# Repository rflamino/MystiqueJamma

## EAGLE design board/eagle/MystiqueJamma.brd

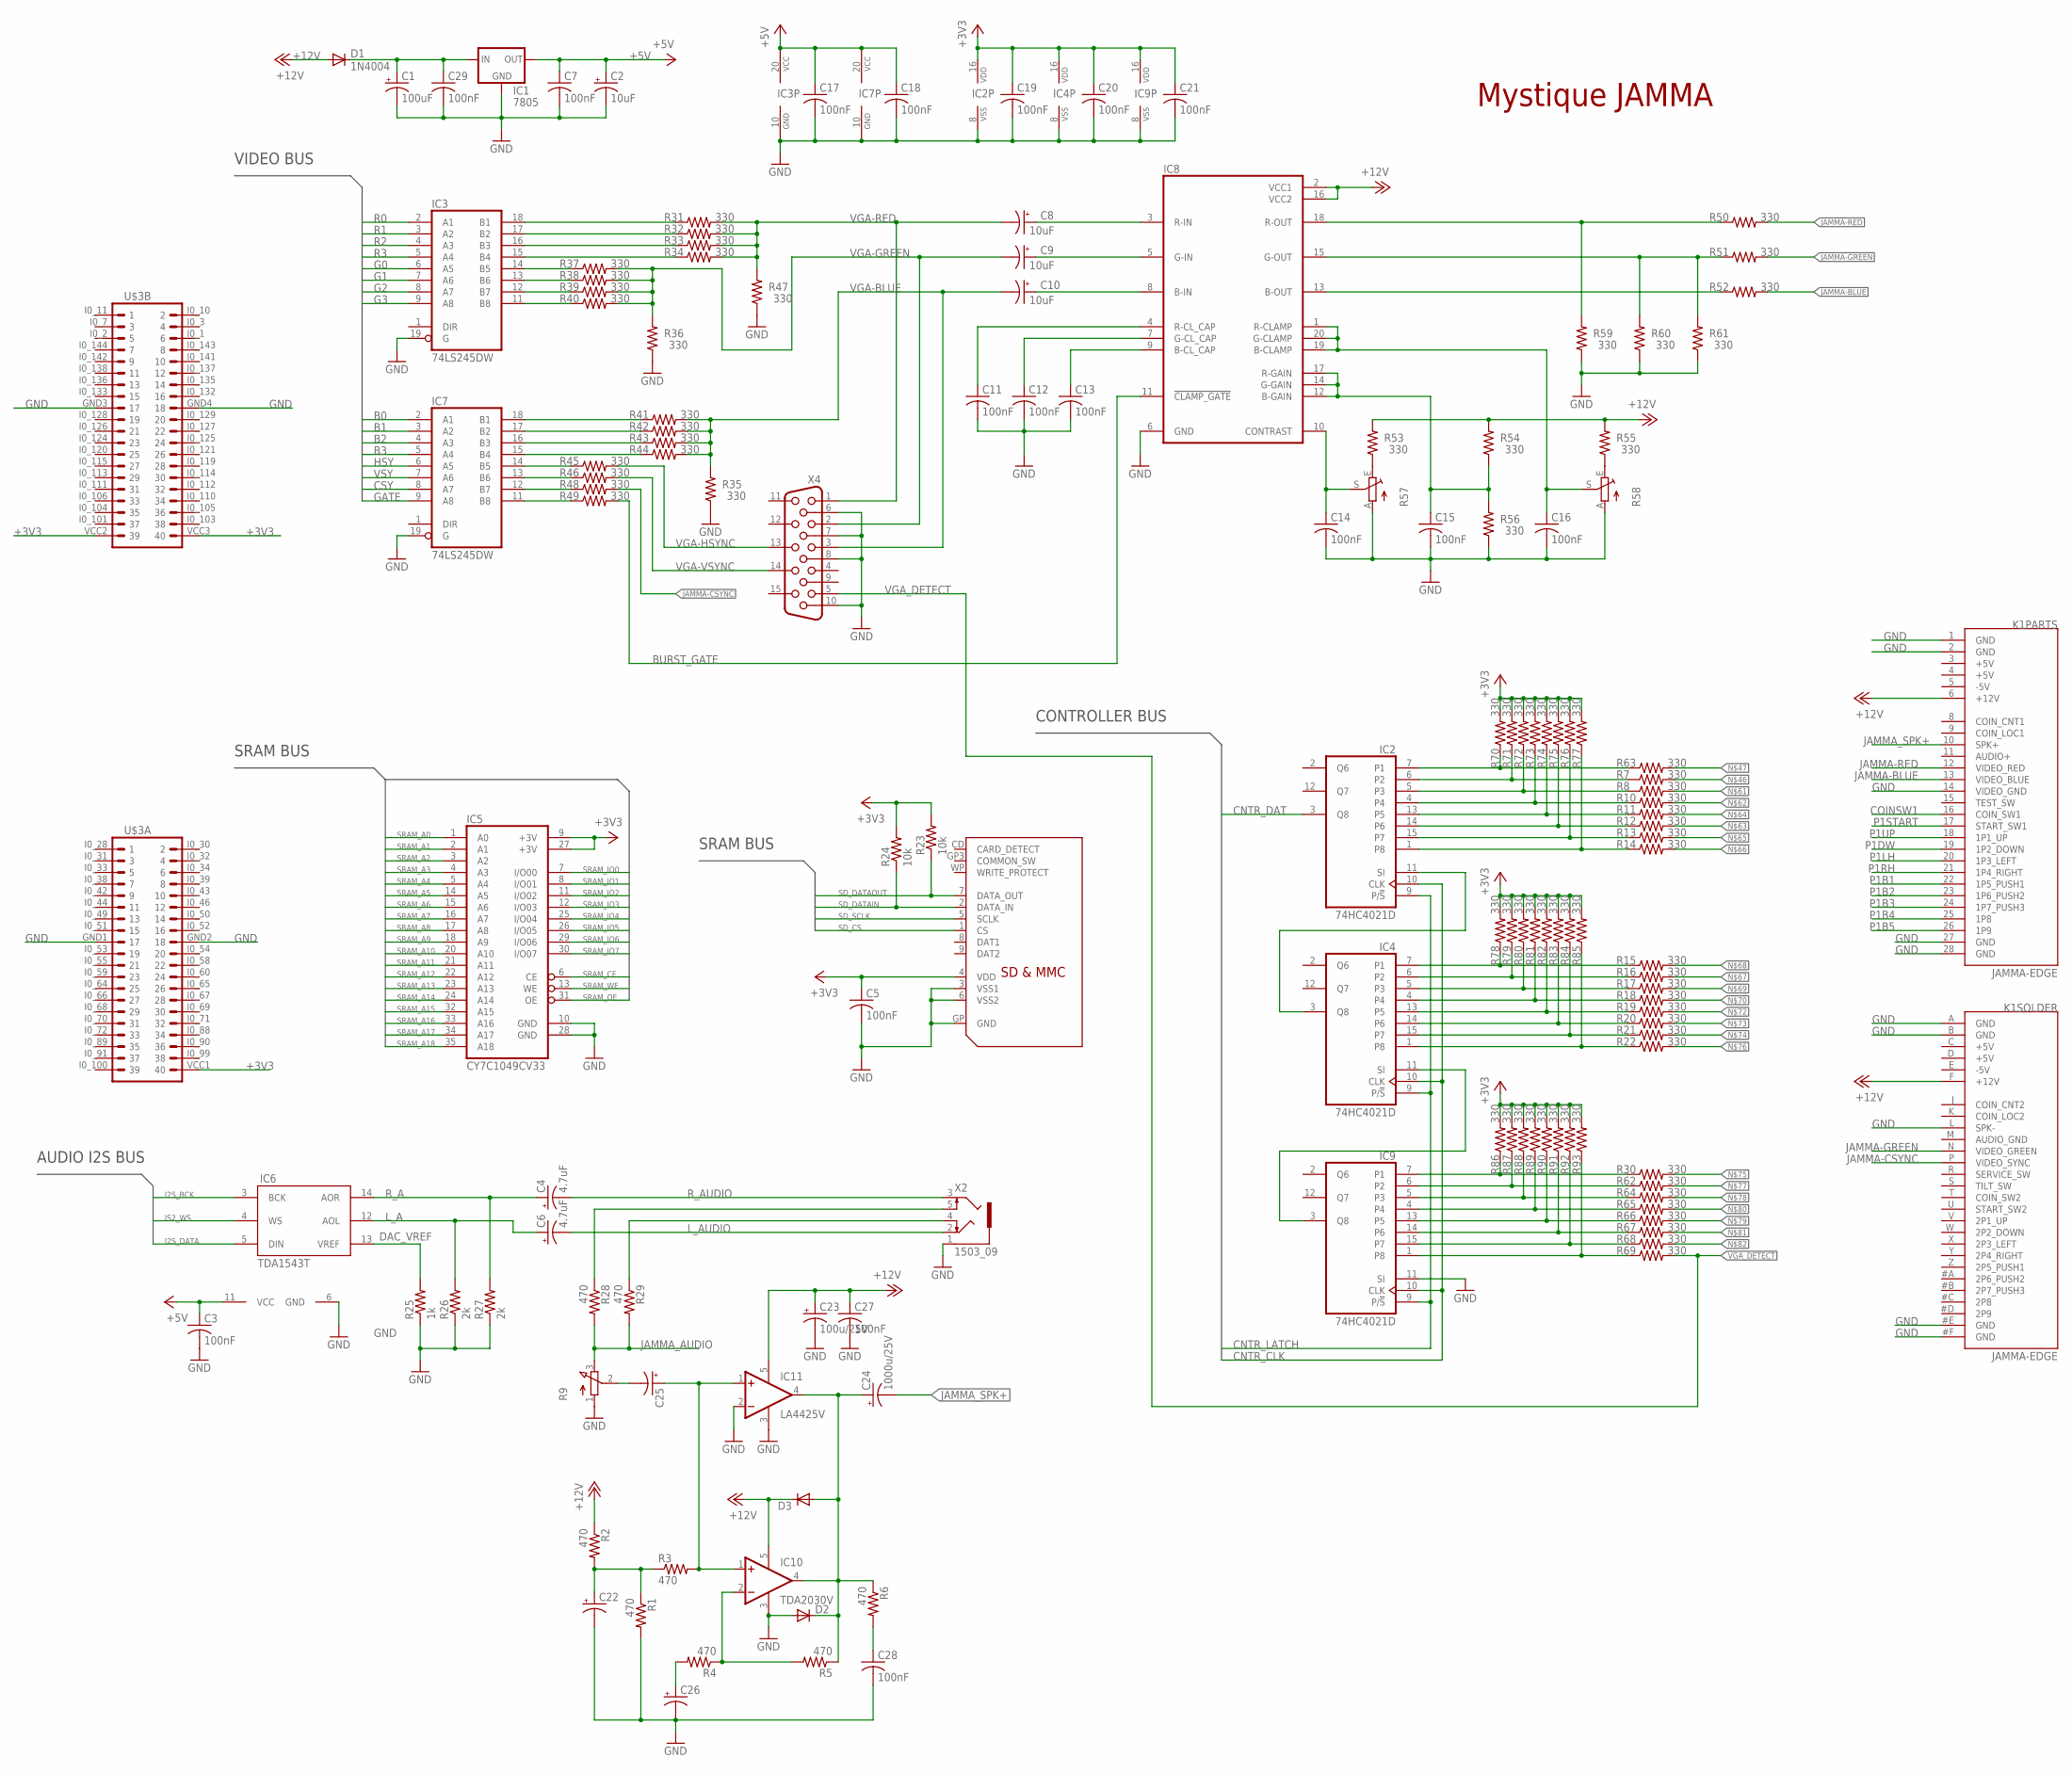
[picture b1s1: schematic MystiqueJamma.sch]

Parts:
C1: 100uF; E2,5-5
C2, C8, C9, C10: 10uF; E2,5-5
C3, C5, C7, C11, C12, C13, C14, C15, C16, C17, C18, C19, C20, C21, C27, C28, C29: 100nF; C1206
C4, C6: 4.7uF; E5-6
C22, C25, C26: CPOL-USE2-4; E2-4
C23: 100u/25V; E3,5-8
C24: 1000u/25V; E3,5-8
D1: 1N4004; DO41-10
D2, D3: DIODE-SOD80C; SOD80C
IC1: 7805; TO220-IGO
IC2, IC4, IC9: 74HC4021D; SO16
IC3, IC7: 74LS245DW; SO20W
IC5: CY7C1049CV33; SOJV36-400
IC6: TDA1543T; SOIC-16NW
IC8: TLS1233; DIL20
IC10: TDA2030V; CB360
IC11: LA4425V; LA4425
K1: JAMMA-EDGE
R1, R2, R3, R4, R5, R6, R28: 470; R1206
R7, R8, R10, R11, R12, R13, R14, R15, R16, R17, R18, R19, R20, R21, R22, R30, R31, R32, R33, R34, R35, R36, R37, R38, R39, R40, R41, R42, R43, R44, R45, R46, R47, R48, R49, R50, R51, R52, R53, R54, R55, R56, R59, R60, R61, R62, R63, R64, R65, R66, R67, R68, R69, R70, R71, R72, R73, R74, R75, R76, R77, R78, R79, R80, R81, R82, R83, R84, R85, R86, R87, R88, R89, R90, R91, R92, R93: 330; M1206
R9: 3RP/1610N
R23, R24: 10k; R1206
R25: 1k; R1206
R26, R27: 2k; R1206
R29: 470; M1206
R57, R58: TRIM_EU-B90P; SP19L
U$2: SDMMC06132; 06132
U$3: C4E6-K""; E6V33
X2: 1503_09
X4: HF15H; HDF15H

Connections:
+3V3: C5.1, C19.1, C20.1, C21.1, IC2.16 (VDD), IC4.16 (VDD), IC5.9 (+3V), IC5.27 (+3V), IC9.16 (VDD), R23.2, R24.2, R70.2, R71.2, R72.2, R73.2, R74.2, R75.2, R76.2, R77.2, R78.2, R79.2, R80.2, R81.2, R82.2, R83.2, R84.2, R85.2, R86.2, R87.2, R88.2, R89.2, R90.2, R91.2, R92.2, R93.2, U$2.4 (VDD), U$3.VCC1 (40), U$3.VCC2 (39), U$3.VCC3 (40)
+5V: C2.+, C3.1, C7.1, C17.1, C18.1, IC1.OUT, IC3.20 (VCC), IC6.11 (VCC), IC7.20 (VCC), K1.3 (+5V), K1.4 (+5V), K1.C (+5V), K1.D (+5V)
+12V: C23.+, C27.1, D1.A, D3.C, IC8.2 (VCC1), IC8.16 (VCC2), IC10.5 (V+), IC11.5 (V+), K1.6 (+12V), K1.F (+12V), R2.1, R53.2, R54.2, R55.2
-5V: K1.5 (-5V), K1.E (-5V)
B0: IC7.2 (A1)
B1: IC7.3 (A2)
B2: IC7.4 (A3)
B3: IC7.5 (A4)
BURST_GATE: IC8.11 (!CLAMP_GATE)
CNTR_CLK: IC2.10 (CLK), IC4.10 (CLK), IC9.10 (CLK)
CNTR_DAT: IC2.3 (Q8)
CNTR_LATCH: IC2.9 (P/!S), IC4.9 (P/!S), IC9.9 (P/!S)
COINSW1: K1.16 (COIN_SW1)
CSY: IC7.8 (A7)
DAC_VREF: IC6.13 (VREF), R25.2
G0: IC3.6 (A5)
G1: IC3.7 (A6)
G2: IC3.8 (A7)
G3: IC3.9 (A8)
GATE: IC7.9 (A8)
GND: C1.-, C2.-, C3.2, C5.2, C7.2, C11.2, C12.2, C13.2, C14.2, C15.2, C16.2, C17.2, C18.2, C19.2, C20.2, C21.2, C22.-, C23.-, C26.-, C27.2, C28.2, C29.2, D2.A, IC1.GND, IC2.8 (VSS), IC3.10 (GND), IC3.19 (G), IC4.8 (VSS), IC5.10 (GND), IC5.28 (GND), IC6.6 (GND), IC7.10 (GND), IC7.19 (G), IC8.6 (GND), IC9.8 (VSS), IC9.11 (SI), IC10.3 (GND), IC11.2 (-IN), IC11.3 (GND), K1.1 (GND), K1.2 (GND), K1.14 (VIDEO_GND), K1.27 (GND), K1.28 (GND), K1.#E (GND), K1.#F (GND), K1.A (GND), K1.B (GND), K1.L (SPK-), R1.2, R9.1 (A), R25.1, R26.1, R27.1, R35.1, R36.1, R47.1, R56.1, R57.A, R58.A, R59.1, R60.1, R61.1, U$2.3 (VSS1), U$2.6 (VSS2), U$2.GP (GND), U$3.GND1 (17), U$3.GND2 (18), U$3.GND3 (17), U$3.GND4 (18), X2.1, X4.6, X4.7, X4.8, X4.10
HSY: IC7.6 (A5)
I2S_BCK: IC6.3 (BCK)
I2S_DATA: IC6.5 (DIN)
IS2_WS: IC6.4 (WS)
JAMMA-BLUE: K1.13 (VIDEO_BLUE), R52.2
JAMMA-CSYNC: K1.P (VIDEO_SYNC)
JAMMA-GREEN: K1.N (VIDEO_GREEN), R51.2
JAMMA-RED: K1.12 (VIDEO_RED), R50.2
JAMMA_AUDIO: R9.3 (E), R28.2, R29.2
JAMMA_SPK+: C24.-, K1.10 (SPK+)
LAA: R29.1, X2.4
L_A: C6.+, IC6.12 (AOL), R26.2
L_AUDIO: C6.-, X2.2
unnamed: IC3.17 (B2), R32.1
unnamed: C1.+, C29.1, D1.C, IC1.IN
unnamed: IC3.18 (B1), R31.1
unnamed: C8.+, IC8.3 (R-IN)
unnamed: C9.+, IC8.5 (G-IN)
unnamed: C10.+, IC8.8 (B-IN)
unnamed: IC3.16 (B3), R33.1
unnamed: IC3.15 (B4), R34.1
unnamed: C16.1, IC8.1 (R-CLAMP), IC8.19 (B-CLAMP), IC8.20 (G-CLAMP), R58.S
unnamed: C11.1, IC8.4 (R-CL_CAP)
unnamed: C12.1, IC8.7 (G-CL_CAP)
unnamed: C13.1, IC8.9 (B-CL_CAP)
unnamed: IC8.18 (R-OUT), R50.1, R59.2
unnamed: IC8.15 (G-OUT), R51.1, R60.2, R61.2
unnamed: IC8.13 (B-OUT), R52.1
unnamed: C14.1, IC8.10 (CONTRAST), R57.S
unnamed: R53.1, R57.E
unnamed: IC2.7 (P1), R63.1
unnamed: R55.1, R58.E
unnamed: IC2.6 (P2), R7.1
unnamed: IC2.5 (P3), R8.1
unnamed: C15.1, IC8.12 (B-GAIN), IC8.14 (G-GAIN), IC8.17 (R-GAIN), R54.1, R56.2
unnamed: IC2.4, R10.1
unnamed: IC2.13 (P5), R11.1
unnamed: IC2.14 (P6), R12.1
unnamed: IC2.15 (P7), R13.1
unnamed: IC2.1 (P8), R14.1
unnamed: C22.+, R1.1, R2.2, R3.1
unnamed: C28.1, R6.2
unnamed: C26.+, R4.2
unnamed: IC10.2 (-IN), R4.1, R5.2
unnamed: IC2.11 (SI), IC4.3 (Q8)
unnamed: IC4.11 (SI), IC9.3 (Q8)
unnamed: C25.-, R9.2 (S)
unnamed: C25.+, IC10.1 (+IN), IC11.1 (+IN), R3.2
unnamed: C24.+, D2.C, D3.A, IC10.4 (OUT), IC11.4 (OUT), R5.1, R6.1
P1B1: K1.22 (1P5_PUSH1)
P1B2: K1.23 (1P6_PUSH2)
P1B3: K1.24 (1P7_PUSH3)
P1B4: K1.25 (1P8)
P1B5: K1.26 (1P9)
P1DW: K1.19 (1P2_DOWN)
P1LH: K1.20 (1P3_LEFT)
P1RH: K1.21 (1P4_RIGHT)
P1START: K1.17 (START_SW1)
P1UP: K1.18 (1P1_UP)
R0: IC3.2 (A1)
R1: IC3.3 (A2)
R2: IC3.4 (A3)
R3: IC3.5 (A4)
RAA: R28.1, X2.5
R_A: C4.+, IC6.14 (AOR), R27.2
R_AUDIO: C4.-, X2.3
SD_CS: U$2.1 (CS)
SD_DATAIN: R24.1, U$2.2 (DATA_IN)
SD_DATAOUT: R23.1, U$2.7 (DATA_OUT)
SD_SCLK: U$2.5 (SCLK)
SRAM_A0: IC5.1 (A0)
SRAM_A1: IC5.2 (A1)
SRAM_A2: IC5.3 (A2)
SRAM_A3: IC5.4 (A3)
SRAM_A4: IC5.5 (A4)
SRAM_A5: IC5.14 (A5)
SRAM_A6: IC5.15 (A6)
SRAM_A7: IC5.16 (A7)
SRAM_A8: IC5.17 (A8)
SRAM_A9: IC5.18 (A9)
SRAM_A10: IC5.20 (A10)
SRAM_A11: IC5.21 (A11)
SRAM_A12: IC5.22 (A12)
SRAM_A13: IC5.23 (A13)
SRAM_A14: IC5.24 (A14)
SRAM_A15: IC5.32 (A15)
SRAM_A16: IC5.33 (A16)
SRAM_A17: IC5.34 (A17)
SRAM_A18: IC5.35 (A18)
SRAM_CE: IC5.6 (CE)
SRAM_IO0: IC5.7 (I/O00)
SRAM_IO1: IC5.8 (I/O01)
SRAM_IO2: IC5.11 (I/O02)
SRAM_IO3: IC5.12 (I/O03)
SRAM_IO4: IC5.25 (I/O04)
SRAM_IO5: IC5.26 (I/O05)
SRAM_IO6: IC5.29 (I/O06)
SRAM_IO7: IC5.30 (I/O07)
SRAM_OE: IC5.31 (OE)
SRAM_WE: IC5.13 (WE)
VGA-BLUE: C10.-, R35.2, X4.3
VGA-GREEN: C9.-, R36.2, X4.2
VGA-HSYNC: X4.13
VGA-RED: C8.-, R31.2, R32.2, R33.2, R34.2, R47.2, X4.1
VGA-VSYNC: X4.14
VGA_DETECT: X4.5
VSY: IC7.7 (A6)

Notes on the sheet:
VIDEO BUS
SRAM BUS
AUDIO I2S BUS
CONTROLLER BUS
Mystique JAMMA

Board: 2 copper layers, 141 parts (1 on the bottom side), 60 nets, no tracks yet.

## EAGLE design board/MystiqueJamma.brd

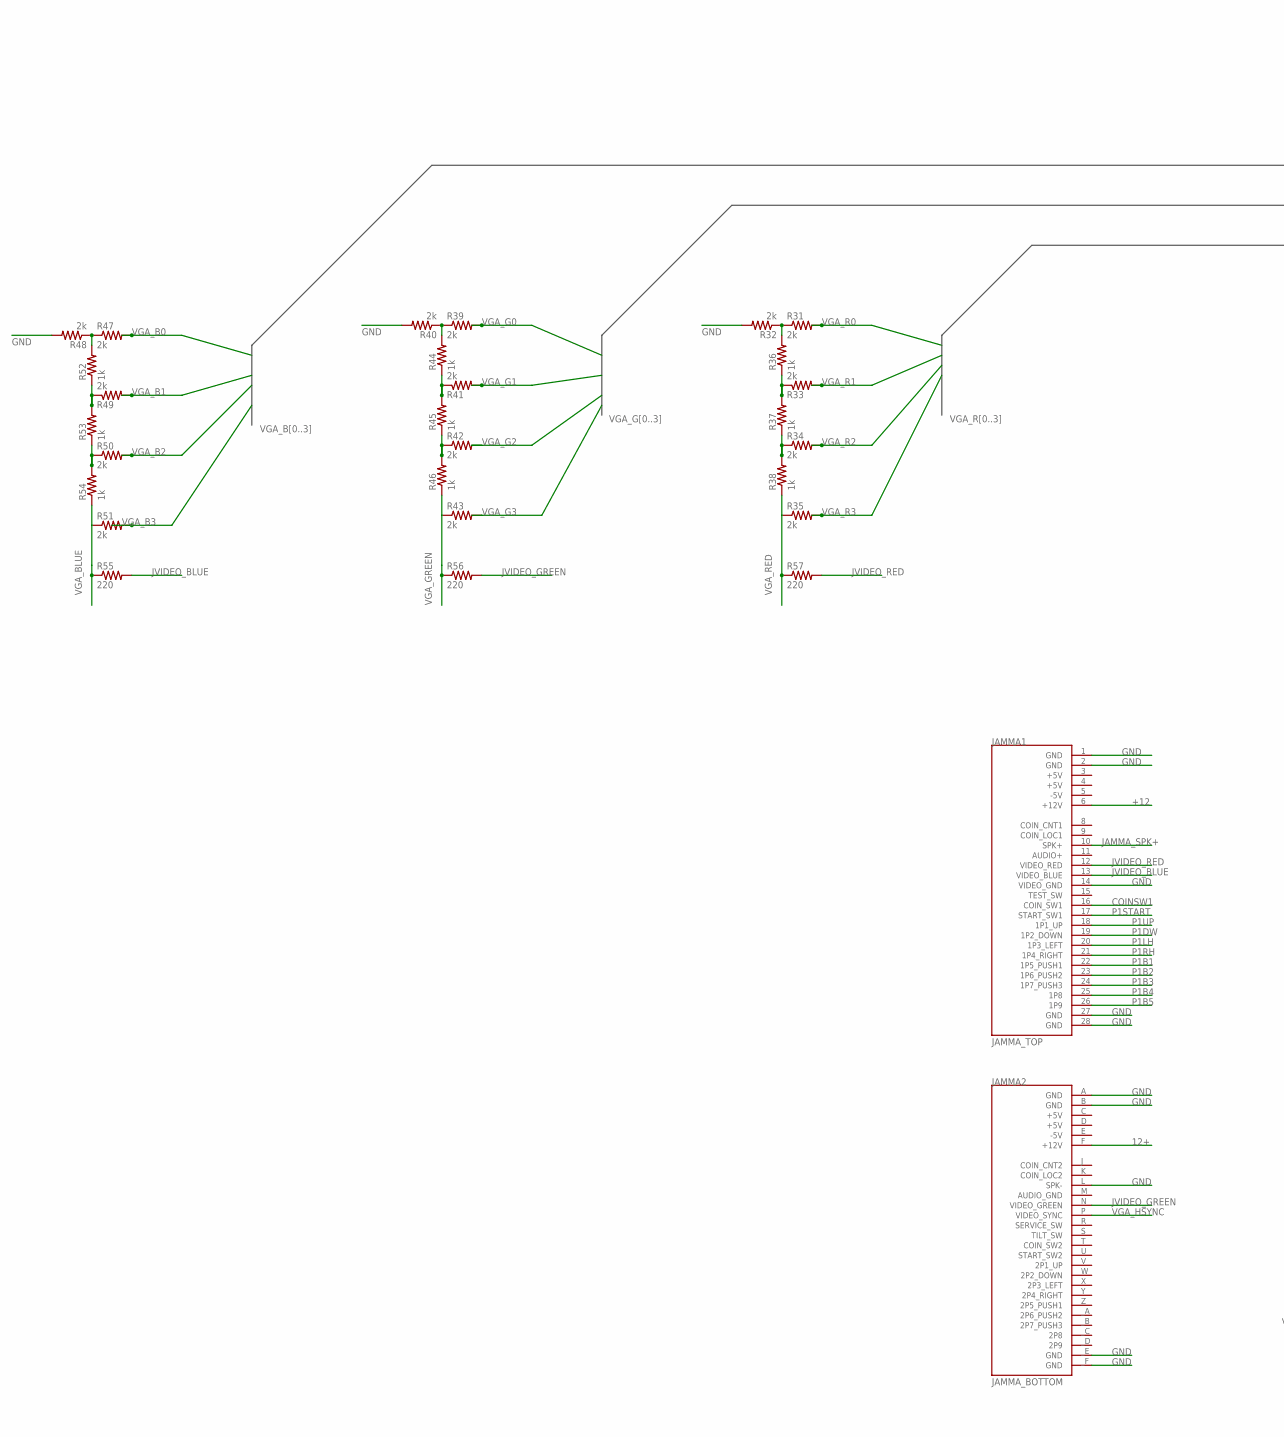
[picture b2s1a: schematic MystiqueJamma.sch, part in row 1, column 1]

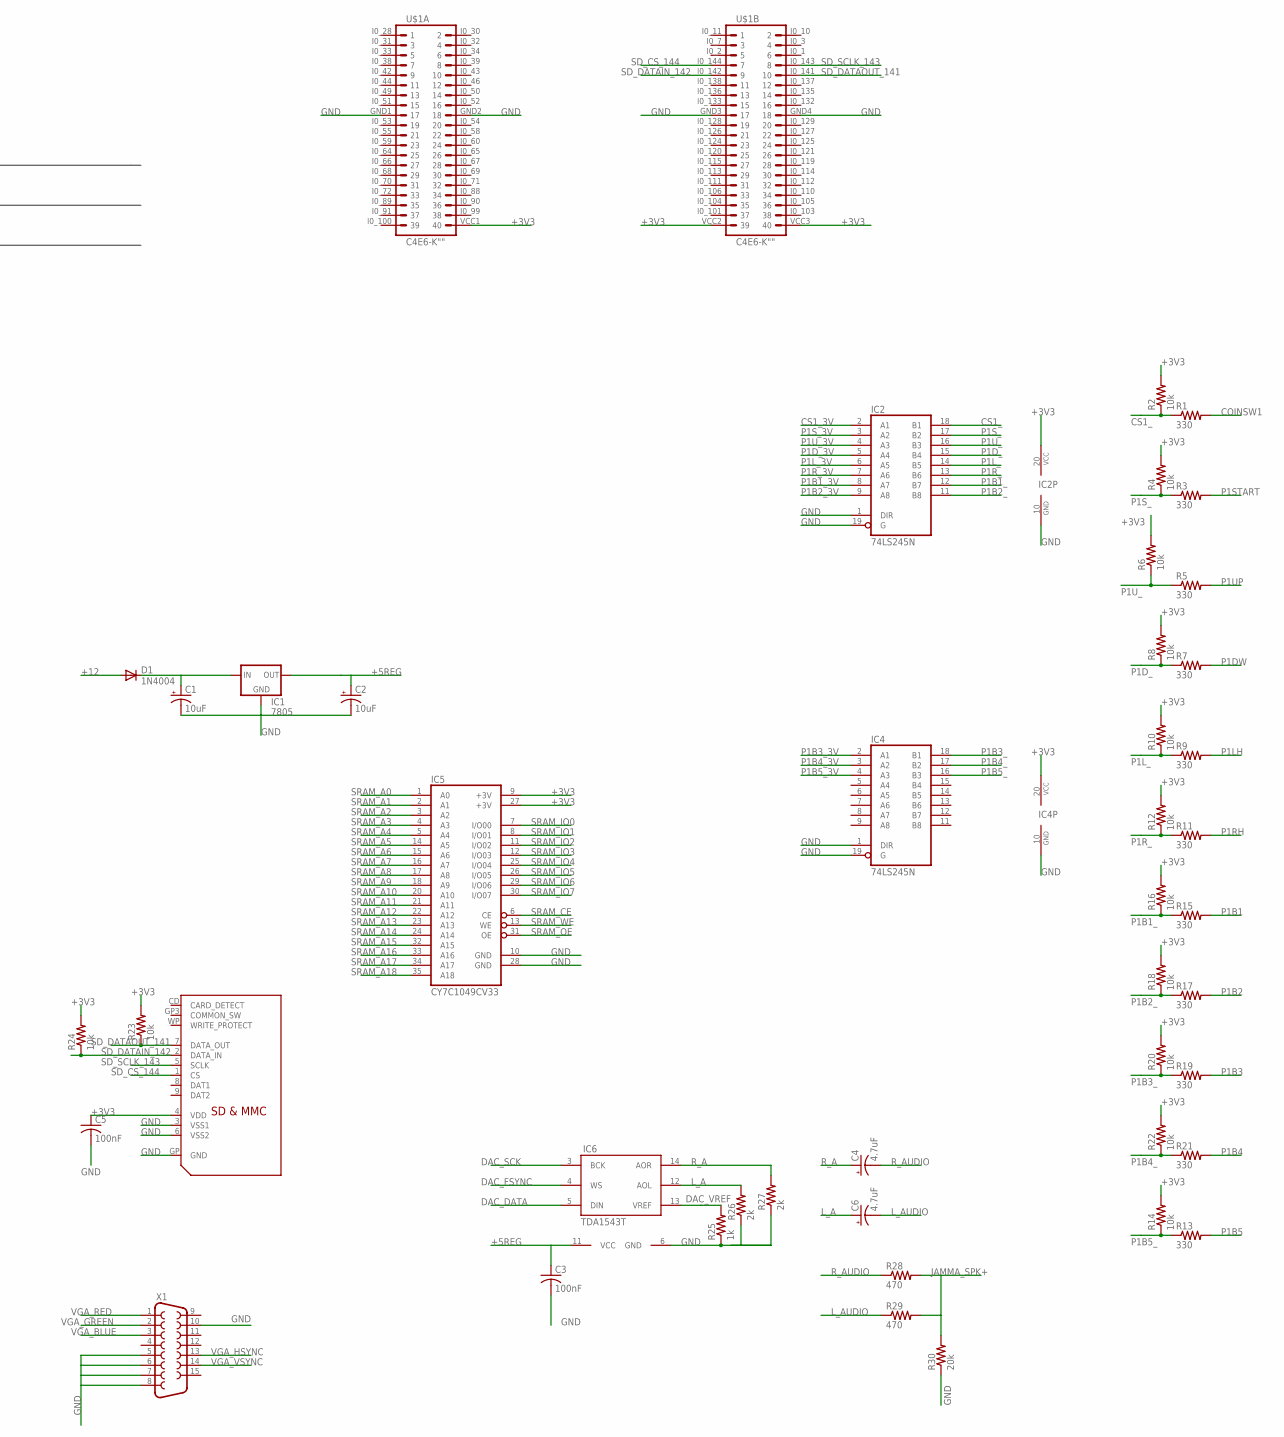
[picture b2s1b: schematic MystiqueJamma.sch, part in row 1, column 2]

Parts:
C1, C2: 10uF; E2,5-5
C3: 100nF; C025-025X050
C4, C6: 4.7uF; E5-6
C5: 100nF; C025-024X044
D1: 1N4004; DO41-10
IC1: 7805; TO220-IGO
IC2, IC4: 74LS245N; DIL20
IC5: CY7C1049CV33; SOJV36-400
IC6: TDA1543T; SOIC-16NW
JAMMA1: JAMMA_TOP
JAMMA2: JAMMA_BOTTOM
R1, R3, R5, R7, R9, R11, R13, R15, R17, R19, R21: 330; 0207/7
R2, R4, R6, R8, R10, R12, R14, R16, R18, R20, R22, R23, R24: 10k; 0207/7
R25, R36, R37, R38, R44, R45, R46, R52, R53, R54: 1k; 0207/7
R26, R27, R31, R32, R33, R34, R35, R39, R40, R41, R42, R43, R47, R48, R49, R50, R51: 2k; 0207/7
R28, R29: 470; 0207/7
R30: 20k; 0207/7
R55, R56, R57: 220; 0207/7
U$1: C4E6-K""; E6V33
U$2: SDMMC06132; 06132
X1: F15HDH; HDF15H

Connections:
12+: JAMMA2.F (+12V)
+3V3: C5.1, IC2.20 (VCC), IC4.20 (VCC), IC5.9 (+3V), IC5.27 (+3V), R2.2, R4.2, R6.2, R8.2, R10.2, R12.2, R14.2, R16.2, R18.2, R20.2, R22.2, R23.2, R24.2, U$1.VCC1 (40), U$1.VCC2 (39), U$2.4 (VDD)
+5REG: C2.+, C3.1, IC1.OUT, IC6.11 (VCC)
+5V: JAMMA1.3 (+5V), JAMMA1.4 (+5V), JAMMA2.C (+5V), JAMMA2.D (+5V)
+12: D1.A, JAMMA1.6 (+12V)
-5V: JAMMA1.5 (-5V), JAMMA2.E (-5V)
COINSW1: JAMMA1.16 (COIN_SW1), R1.2
CS1_: IC2.18 (B1), R1.1, R2.1
CS1_3V: IC2.2 (A1)
DAC_DATA: IC6.5 (DIN)
DAC_FSYNC: IC6.4 (WS)
DAC_SCK: IC6.3 (BCK)
DAC_VREF: IC6.13 (VREF), R25.2
GND: C1.-, C2.-, C3.2, C5.2, IC1.GND, IC2.1 (DIR), IC2.10 (GND), IC2.19 (G), IC4.1 (DIR), IC4.10 (GND), IC4.19 (G), IC5.10 (GND), IC5.28 (GND), IC6.6 (GND), JAMMA1.1 (GND), JAMMA1.2 (GND), JAMMA1.14 (VIDEO_GND), JAMMA1.27 (GND), JAMMA1.28 (GND), JAMMA2.A (GND), JAMMA2.B (GND), JAMMA2.L (SPK-), JAMMA2._E (GND), JAMMA2._F (GND), R25.1, R26.1, R27.1, R30.1, R32.2, R40.2, R48.2, U$1.GND1 (17), U$1.GND2 (18), U$1.GND3 (17), U$1.GND4 (18), U$2.3 (VSS1), U$2.6 (VSS2), U$2.GP (GND), X1.5, X1.10
JAMMA_SPK+: JAMMA1.10 (SPK+), R28.2, R29.2, R30.2
JVIDEO_BLUE: JAMMA1.13 (VIDEO_BLUE), R55.2
JVIDEO_GREEN: JAMMA2.N (VIDEO_GREEN), R56.2
JVIDEO_RED: JAMMA1.12 (VIDEO_RED), R57.2
L_A: C6.+, IC6.12 (AOL), R26.2
L_AUDIO: C6.-, R29.1
unnamed: R31.1, R32.1, R36.2
unnamed: C1.+, D1.C, IC1.IN
unnamed: R33.1, R36.1, R37.2
unnamed: R34.1, R37.1, R38.2
unnamed: R39.1, R40.1, R44.2
unnamed: R41.1, R44.1, R45.2
unnamed: R42.1, R45.1, R46.2
unnamed: R47.1, R48.1, R52.2
unnamed: R49.1, R52.1, R53.2
unnamed: R50.1, R53.1, R54.2
P1B1: JAMMA1.22 (1P5_PUSH1), R15.2
P1B1_: IC2.12 (B7), R15.1, R16.1
P1B1_3V: IC2.8 (A7)
P1B2: JAMMA1.23 (1P6_PUSH2), R17.2
P1B2_: IC2.11 (B8), R17.1, R18.1
P1B2_3V: IC2.9 (A8)
P1B3: JAMMA1.24 (1P7_PUSH3), R19.2
P1B3_: IC4.18 (B1), R19.1, R20.1
P1B3_3V: IC4.2 (A1)
P1B4: JAMMA1.25 (1P8), R21.2
P1B4_: IC4.17 (B2), R21.1, R22.1
P1B4_3V: IC4.3 (A2)
P1B5: JAMMA1.26 (1P9), R13.2
P1B5_: IC4.16 (B3), R13.1, R14.1
P1B5_3V: IC4.4 (A3)
P1DW: JAMMA1.19 (1P2_DOWN), R7.2
P1D_: IC2.15 (B4), R7.1, R8.1
P1D_3V: IC2.5 (A4)
P1LH: JAMMA1.20 (1P3_LEFT), R9.2
P1L_: IC2.14 (B5), R9.1, R10.1
P1L_3V: IC2.6 (A5)
P1RH: JAMMA1.21 (1P4_RIGHT), R11.2
P1R_: IC2.13 (B6), R11.1, R12.1
P1R_3V: IC2.7 (A6)
P1START: JAMMA1.17 (START_SW1), R3.2
P1S_: IC2.17 (B2), R3.1, R4.1
P1S_3V: IC2.3 (A2)
P1UP: JAMMA1.18 (1P1_UP), R5.2
P1U_: IC2.16 (B3), R5.1, R6.1
P1U_3V: IC2.4 (A3)
R_A: C4.+, IC6.14 (AOR), R27.2
R_AUDIO: C4.-, R28.1
SD_CS_144: U$1.I0_144 (7), U$2.1 (CS)
SD_DATAIN_142: R24.1, U$1.I0_142 (9), U$2.2 (DATA_IN)
SD_DATAOUT_141: R23.1, U$1.I0_141 (10), U$2.7 (DATA_OUT)
SD_SCLK_143: U$1.I0_143 (8), U$2.5 (SCLK)
SRAM_A0: IC5.1 (A0)
SRAM_A1: IC5.2 (A1)
SRAM_A2: IC5.3 (A2)
SRAM_A3: IC5.4 (A3)
SRAM_A4: IC5.5 (A4)
SRAM_A5: IC5.14 (A5)
SRAM_A6: IC5.15 (A6)
SRAM_A7: IC5.16 (A7)
SRAM_A8: IC5.17 (A8)
SRAM_A9: IC5.18 (A9)
SRAM_A10: IC5.20 (A10)
SRAM_A11: IC5.21 (A11)
SRAM_A12: IC5.22 (A12)
SRAM_A13: IC5.23 (A13)
SRAM_A14: IC5.24 (A14)
SRAM_A15: IC5.32 (A15)
SRAM_A16: IC5.33 (A16)
SRAM_A17: IC5.34 (A17)
SRAM_A18: IC5.35 (A18)
SRAM_CE: IC5.6 (CE)
SRAM_IO0: IC5.7 (I/O00)
SRAM_IO1: IC5.8 (I/O01)
SRAM_IO2: IC5.11 (I/O02)
SRAM_IO3: IC5.12 (I/O03)
SRAM_IO4: IC5.25 (I/O04)
SRAM_IO5: IC5.26 (I/O05)
SRAM_IO6: IC5.29 (I/O06)
SRAM_IO7: IC5.30 (I/O07)
SRAM_OE: IC5.31 (OE)
SRAM_WE: IC5.13 (WE)
VGA_B0: R47.2
VGA_B1: R49.2
VGA_B2: R50.2
VGA_B3: R51.2
VGA_BLUE: R51.1, R54.1, R55.1, X1.3
VGA_G0: R39.2
VGA_G1: R41.2
VGA_G2: R42.2
VGA_G3: R43.2
VGA_GREEN: R43.1, R46.1, R56.1, X1.2
VGA_HSYNC: JAMMA2.P (VIDEO_SYNC), X1.13
VGA_R0: R31.2
VGA_R1: R33.2
VGA_R2: R34.2
VGA_R3: R35.2
VGA_RED: R35.1, R38.1, R57.1, X1.1
VGA_VSYNC: X1.14

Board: 2 copper layers, 74 parts (0 on the bottom side), 55 nets, no tracks yet.

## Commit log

2018-08-28 MystiqueJamma files
    initial commit
2018-08-28 created folder board
2018-08-28 included jamma eagle lib
2018-08-28 included pdf file
2018-09-03 jamma spacing change
2018-09-10 included sdcard
2018-09-10 docs
2018-09-12 changed sram ic
2018-09-16 wiring up!
2018-09-16 pictures
2018-09-17 pdf file
2018-09-17 added gitignore for eagle files
2018-09-18 deleted temp files
2018-09-22 documents
2018-09-22 photos
2018-09-23 changed the jamma connector and included audio TDA1543
2018-09-23 fpga board pictures
2018-09-24 protel 99 file from fpga board
2018-09-25 audio circuit update
2018-09-25 audio circuit
2018-09-25 Eagle library for FPGA board
    Eagle library for FPGA board. Dimensions and components placement as received from manufacturer and have small misalignments (< 5 mils)
2018-09-25 video circuit
2018-09-25 included the FPGA board library
2018-09-25 Added reference Pinouts
    Added reference pinouts, changed board outline to TPlace like a component
2018-09-26 Added TLS1233 video amplifier IC library
2018-09-26 more video docs
2018-09-26 Added spreadsheet with pin usage
2018-09-26 xls list
2018-09-27 kicad project
2018-09-27 kicad board layout
2018-09-27 kicad
2018-09-28 Shift registers to read controllers, new libs
2018-09-28 Updated pinouts, added docs
2018-09-28 Added DAC calculation tab on spreadsheet
2018-10-07 FPGA board pins now defined
2018-10-10 Added volume potentiometer footprint
2018-10-23 Added MOLEX power connector
2018-10-23 Added edge cut for JTAG header
2018-10-25 Edge connector pins associated with shift registers
2018-10-26 First completed layout
2018-10-31 routing and footprints enhancement
2018-10-31 discarded old file
2018-11-07 Added Mini DIN6 Connector
2018-11-09 Added Logo, arranged component labels
2018-11-12 Removed old directory updated schematics
2018-11-12 board pictures tryout
2018-11-23 Updated component values
2018-11-25 vga test
2018-11-25 VGA test core files
2018-11-30 Added second SRAM, Match FPGA IO usage with board available pins
2018-12-05 Circuit update and cleanup
    Added second SRAM, changed VGA detect to FPGA instead of shift registers, added solder joint to force VGA mode, added RC-Network to Shift Register clock signal to allow same line to control LATCH sig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
2018-12-19 Added Micro SD card connector
